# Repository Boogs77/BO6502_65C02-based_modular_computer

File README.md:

# BO6502: 65C02-Based Modular Computer System

Technical overview of the **BO6502** core architecture. This system leverages the iconic 6502 instruction set with modern, high-reliability components from Western Design Center, Atmel, and Hitachi, offering a versatile platform for retro-computing enthusiasts.

---

## 🧠 Processing Core & System Control

The system is built around a modular 39-pin bus (36 signals + 3 spares) distributed via a robust backplane.

| Module | Type | Status | Description |
| :--- | :--- | :--- | :--- |
| **[CPU Module](https://github.com/Boogs77/BO6502/tree/main/BO6502%20CPU)** |  |  | Central Processing Unit W65C02S. |
| **[Reset & Clock](https://github.com/Boogs77/BO6502/tree/main/BO6502%20RESET)** |  |  | NE555 Reset and switchable clock (2MHz/1MHz/500kHz). |
| **[Backplate](https://github.com/Boogs77/BO6502/tree/main/BO6502%20BACKPLATE)** |  |  | The 39-pin bus backbone with voltage regulation. |
| **[Bridge Connector](https://github.com/Boogs77/BO6502/tree/main/BO6502%20CONNECTOR)** |  |  | Interconnect for daisy-chaining multiple backplates. |

---

## 💾 Memory Map & Storage

The system features a balanced 64KB memory architecture, divided between high-speed static RAM and non-volatile storage.

### [RAM Module](https://github.com/Boogs77/BO6502/tree/main/BO6502%20RAM) ($0000 - $7FFF)
* **Chip**: HITACHI **HM62256LP-12** (32KB SRAM).
* **Status**: 
* **Features**: Revision 02 includes **8 exclusion jumpers** (J-CS0 to J-CS7) to carve out space for I/O modules. Includes JP4 to bypass system clock triggering.
* **PCB**: [RAM_final_rev02](https://github.com/Boogs77/BO6502/blob/main/BO6502%20RAM/gallery/RAM_final_rev02.png?raw=true).

### [ROM Module](https://github.com/Boogs77/BO6502/tree/main/BO6502%20ROM) ($8000 - $FFFF)
* **Chip**: ATMEL **AT28C256** (32KB EEPROM).
* **Status**: 
* **Features**: Equipped with a **ZIF socket** for easy updates. The "Multi" version uses jumpers (J-CS3, CS4, CS5) to disable ROM in specific ranges for advanced peripherals.
* **PCBs**: [Base](https://github.com/Boogs77/BO6502_65C02-based_modular_computer/blob/main/BO6502%20ROM/gallery/ROM_final_rev01.png?raw=true) | [24K Test](https://github.com/Boogs77/BO6502_65C02-based_modular_computer/blob/main/BO6502%20ROM/gallery/ROM24k_final_rev01.png?raw=true) | [Multi-Selection](https://github.com/Boogs77/BO6502_65C02-based_modular_computer/blob/main/BO6502%20ROM/gallery/ROMmulti_final_rev01.png?raw=true).

---

## 🔌 Peripheral & I/O Addressing

Peripheral addressing is managed via **74LS138** decoders to ensure precise memory mapping and avoid bus contention.

| Module | Type | Status | Address | PCB Link |
| :--- | :--- | :--- | :--- | :--- |
| **[VDU Module](https://github.com/Boogs77/BO6502/tree/main/BO6502%20VDU)** |  |  | **$BXXX** | [VDU PCB](https://github.com/Boogs77/BO6502_65C02-based_modular_computer/blob/main/BO6502%20VDU/gallery/VDU_TMS_final_rev01.png?raw=true) |
| **[Serial I/O](https://github.com/Boogs77/BO6502/tree/main/BO6502%20SERIAL)** |  |  | **$CXXX** | [Serial PCB](https://github.com/Boogs77/BO6502_65C02-based_modular_computer/blob/main/BO6502%20SERIAL/gallery/Serial_final_rev03.png?raw=true) |
| **[SD Card](https://github.com/Boogs77/BO6502/tree/main/BO6502%20SDCard)** |  |  | **$D1BX** | [SD Card PCB](https://github.com/Boogs77/BO6502_65C02-based_modular_computer/blob/main/BO6502%20SDCard/gallery/SDcard_final_rev02%20v2.png?raw=true) |
| **[Standalone Keyb](https://github.com/Boogs77/BO6502/tree/main/BO6502%20KEYb)** |  |  | **$D18X** | [Keyboard PCB](https://github.com/Boogs77/BO6502/blob/main/BO6502%20KEYb/gallery/KEYb_final-rev01.png?raw=true) |
| **[Big LCD Module](https://github.com/Boogs77/BO6502/tree/main/BO6502%20BIGLCD)** |  |  | **$D19X** | [Big LCD Module](https://github.com/Boogs77/BO6502/blob/main/BO6502%20BIGLCD/README.md) |
| **[Legacy LCD/Keyb](https://github.com/Boogs77/BO6502/tree/main/BO6502%20LCD_KEYb)** |  |  | **$DXXX** | [Legacy PCB](https://github.com/Boogs77/BO6502/blob/main/BO6502%20LCD_KEYb/gallery/LCD_KEYb_final_rev02.png?raw=true) |

---

## 📺 Visual Output Tiers

* **Pro**: **TMS9918A** VDU Module with 32KB dedicated RAM. Supports NTSC Composite Out, Sprites, and 16 Colors.
* **Advanced**: **Toshiba T6963** Graphical LCD (160x128 Pixels).
* **Basic**: **Hitachi HD44780U** 16x2 Character LCD.

---

## 🛠 Diagnostic & Testing Tools

| Module | Type | Status | Function | PCB Link |
| :--- | :--- | :--- | :--- | :--- |
| **[Monitor Interface](https://github.com/Boogs77/BO6502/tree/main/BO6502%20MONITOR)** |  |  | Arduino Mega Bus Sniffer (Ben Eater style). | [Monitor PCB](https://github.com/Boogs77/BO6502/blob/main/BO6502%20MONITOR/gallery/MONITOR_final_rev01.png?raw=true) |
| **[LED Test Board](https://github.com/Boogs77/BO6502/tree/main/BO6502%20LED)** |  |  | Visual 16-LED debug for VIA 65C22 ports. | [LED PCB](https://github.com/Boogs77/BO6502/blob/main/BO6502%20LED/gallery/led_final.png?raw=true) |

---

## 📐 Important Technical Notes

### Jumper Configuration for Advanced Modules
When using the latest system modules (VDU, Joystick, SD Card, etc.), the **ROM** and **RAM** modules must be configured to prevent address conflicts:
- **ROM J-CS3/CS4/CS5**: Set to **VCC** to disable ROM in those specific I/O ranges.
- **SD Card Access**: Provides **Raw Data Access** via bit-banged SPI (PA1=MISO, PA2=MOSI, PA3=SCK, PA4=CS).

---
© 2026 Boogs77 | BO6502 Project - Technical Documentation.

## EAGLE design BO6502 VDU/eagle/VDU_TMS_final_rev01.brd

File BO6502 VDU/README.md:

# BO6502 VDU (Video Display Unit)

The **VDU Module** brings advanced color graphics and video capabilities to the BO6502 system. It is built around the legendary **TMS9918A** Video Display Processor (VDP), the same chip found in iconic systems like the MSX, ColecoVision, and TI-99/4A.

---

## 🛠 Hardware Specifications

The design of this module is the result of extensive research and optimization, integrating modern memory solutions with vintage video hardware.

* **Video Processor:** **TMS9918A** alowing for multiple video modes, including 15 colors plus transparent, and sprite support.
* **Video RAM:** Utilizes an **HM62256** (32KB SRAM) chip. Although the TMS9918A natively addresses 16KB, this modern SRAM provides a stable and reliable memory interface.
* **Logic Optimization:** Following the analysis of the **[HBC-56 project](https://github.com/visrealm/hbc-56/tree/main/schematics/tms9918)**, the design opts for a **74HCT245** transceiver instead of a third 74HCT574 latch. This choice streamlines the data bus communication between the CPU and the VDP.

### Design References
The architecture is heavily inspired by:
* **Leonardo Milani's work:** [Interfacing a TMS9918A to a 6502](https://www.leonardomiliani.com/?p=1631&lang=en).
* **J.B. Langston's design:** [TMS9918A Interface](https://github.com/jblang/TMS9918A).

---

## 🕹️ Address Decoding ($BXXX)

The module is integrated into the system memory map using a **74HCT138** decoder.

* **Address Range:** The VDU is mapped to the **$BXXX** block.
* **Interface:** The CPU communicates with the VDP via two specific addresses within this range to handle data transfers and register configurations.

---

## 📐 Development & Testing

Before the final PCB production, the board underwent rigorous testing:
* **Arduino Integration:** Extensive tests were performed using an **Arduino Mega** to verify the correct addressing logic and to validate all supported video modes (Text, Multicolour, Graphics I & II).
* **Signal Integrity:** Careful layout was implemented to ensure the composite video output remains clean and free from interference.

---

## 📂 Related Modules
* 🏗️ **[Backplate System](https://github.com/Boogs77/BO6502/blob/main/BO6502%20BACKPLATE/README.md)**: Main 39-pin system bus connection.
* 🧠 **[CPU Module](https://github.com/Boogs77/BO6502/blob/main/BO6502%20CPU/README.md)**: W65C02 central processor.
* 🖥️ **[Monitor Interface](https://github.com/Boogs77/BO6502/blob/main/BO6502%20MONITOR/README.md)**: Used during early VDP register debugging.

---
© 2026 Boogs77 | BO6502 Project - Technical Documentation.

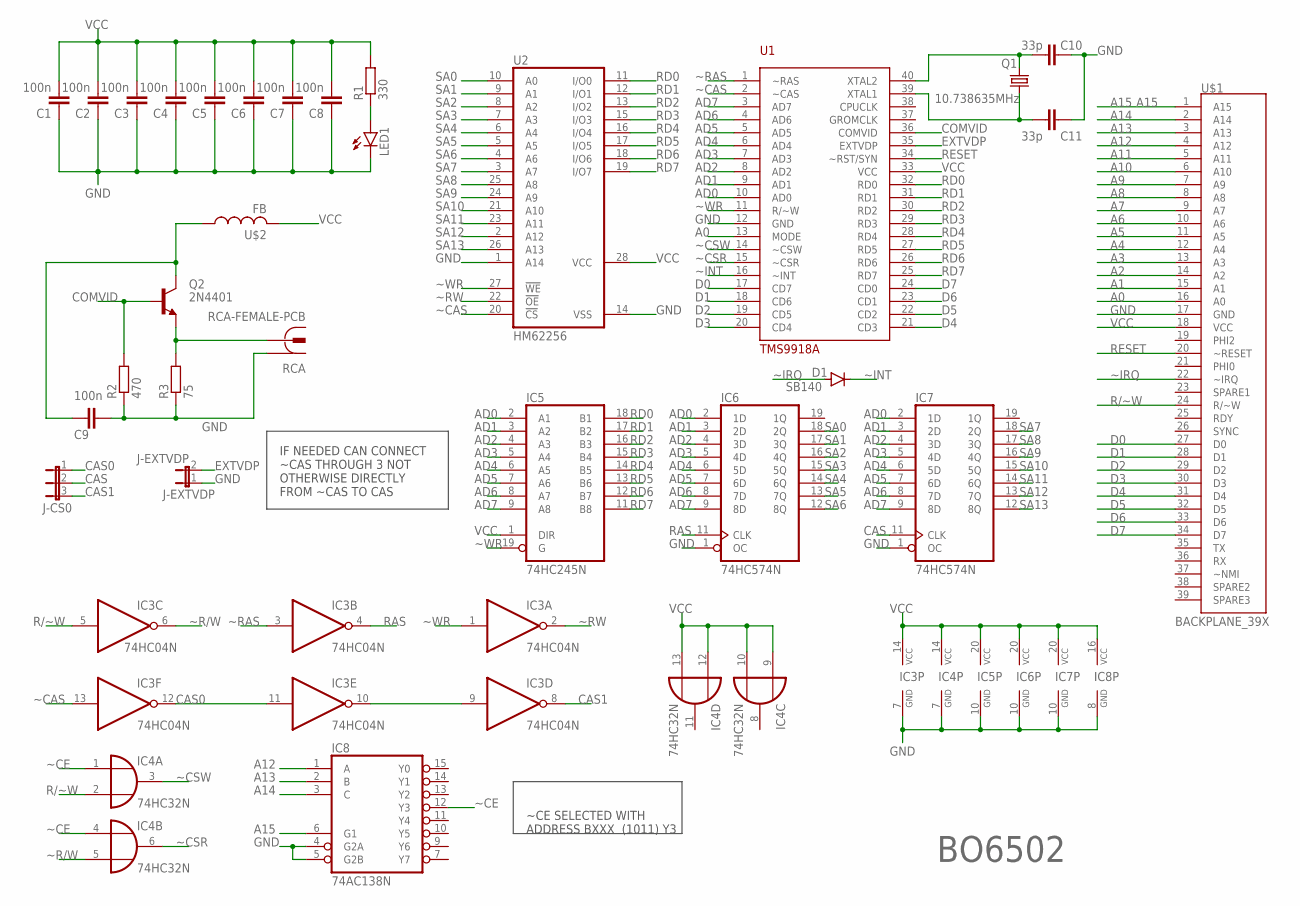
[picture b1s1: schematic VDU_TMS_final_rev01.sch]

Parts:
C1, C2, C3, C4, C5, C6, C7, C8, C9: 100n; C025-025X050
C10, C11: 33p; C025-025X050
D1: SB140; DO41-10
IC3: 74HC04N; DIL14
IC4: 74HC32N; DIL14
IC5: 74HC245N; DIL20
IC6, IC7: 74HC574N; DIL20
IC8: 74AC138N; DIL16
J-CAS: J-CS0; JP2
J-EXTVDP: J-EXTVDP; JP1
LED1: RED; LED5MM
Q1: 10.738635MHz; HC49/S
Q2: 2N4401; TO92-EBC
R1: 330; 0207/10
R2: 470; 0207/10
R3: 75; 0207/10
RCA: RCA-FEMALE-PCB
U1: TMS9918A; DIL40
U2: HM62256; DIL28-6
U$1: BACKPLANE_39X; BP_39X
U$2: FB

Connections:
A0: U1.13 (MODE), U$1.16 (A0)
A1: U$1.15 (A1)
A2: U$1.14 (A2)
A3: U$1.13 (A3)
A4: U$1.12 (A4)
A5: U$1.11 (A5)
A6: U$1.10 (A6)
A7: U$1.9 (A7)
A8: U$1.8 (A8)
A9: U$1.7 (A9)
A10: U$1.6 (A10)
A11: U$1.5 (A11)
A12: IC8.1 (A), U$1.4 (A12)
A13: IC8.2 (B), U$1.3 (A13)
A14: IC8.3 (C), U$1.2 (A14)
A15: IC8.6 (G1), U$1.1 (A15)
AD0: IC5.2 (A1), IC6.2 (1D), IC7.2 (1D), U1.10 (AD0)
AD1: IC5.3 (A2), IC6.3 (2D), IC7.3 (2D), U1.9 (AD1)
AD2: IC5.4 (A3), IC6.4 (3D), IC7.4 (3D), U1.8 (AD2)
AD3: IC5.5 (A4), IC6.5 (4D), IC7.5 (4D), U1.7 (AD3)
AD4: IC5.6 (A5), IC6.6 (5D), IC7.6 (5D), U1.6 (AD4)
AD5: IC5.7 (A6), IC6.7 (6D), IC7.7 (6D), U1.5 (AD5)
AD6: IC5.8 (A7), IC6.8 (7D), IC7.8 (7D), U1.4 (AD6)
AD7: IC5.9 (A8), IC6.9 (8D), IC7.9 (8D), U1.3 (AD7)
CAS: IC7.11 (CLK), J-CAS.2
CAS0: IC3.11 (I), IC3.12 (O), J-CAS.1
CAS1: IC3.8 (O), J-CAS.3
COMVID: Q2.B, R2.2, U1.36 (COMVID)
D0: U1.17 (CD7), U$1.27 (D0)
D1: U1.18 (CD6), U$1.28 (D1)
D2: U1.19 (CD5), U$1.29 (D2)
D3: U1.20 (CD4), U$1.30 (D3)
D4: U1.21 (CD3), U$1.31 (D4)
D5: U1.22 (CD2), U$1.32 (D5)
D6: U1.23 (CD1), U$1.33 (D6)
D7: U1.24 (CD0), U$1.34 (D7)
EXTVDP: J-EXTVDP.2, U1.35 (EXTVDP)
GND: C1.1, C2.1, C3.1, C4.1, C5.1, C6.1, C7.1, C8.1, C9.1, C10.1, C11.1, IC3.7 (GND), IC4.7 (GND), IC5.10 (GND), IC6.1 (OC), IC6.10 (GND), IC7.1 (OC), IC7.10 (GND), IC8.4 (G2A), IC8.5 (G2B), IC8.8 (GND), J-EXTVDP.1, LED1.K (C), R2.1, R3.1, RCA.1, U1.12 (GND), U2.1 (A14), U2.14 (VSS), U$1.17 (GND)
unnamed: Q2.E, R3.2, RCA.2@1 (2), RCA.2@2 (2)
unnamed: C9.2, Q2.C, U$2.P$1 (1)
unnamed: C10.2, Q1.2, U1.40 (XTAL2)
unnamed: LED1.A, R1.1
unnamed: C11.2, Q1.1, U1.39 (XTAL1)
unnamed: IC3.9 (I), IC3.10 (O)
R/~W: IC3.5 (I), IC4.2 (I1), U$1.24 (R/~W)
RAS: IC3.4 (O), IC6.11 (CLK)
RD0: IC5.18 (B1), U1.32 (RD0), U2.11 (I/O0)
RD1: IC5.17 (B2), U1.31 (RD1), U2.12 (I/O1)
RD2: IC5.16 (B3), U1.30 (RD2), U2.13 (I/O2)
RD3: IC5.15 (B4), U1.29 (RD3), U2.15 (I/O3)
RD4: IC5.14 (B5), U1.28 (RD4), U2.16 (I/O4)
RD5: IC5.13 (B6), U1.27 (RD5), U2.17 (I/O5)
RD6: IC5.12 (B7), U1.26 (RD6), U2.18 (I/O6)
RD7: IC5.11 (B8), U1.25 (RD7), U2.19 (I/O7)
RESET: U1.34 (~RST/SYN), U$1.20 (~RESET)
SA0: IC6.18 (2Q), U2.10 (A0)
SA1: IC6.17 (3Q), U2.9 (A1)
SA2: IC6.16 (4Q), U2.8 (A2)
SA3: IC6.15 (5Q), U2.7 (A3)
SA4: IC6.14 (6Q), U2.6 (A4)
SA5: IC6.13 (7Q), U2.5 (A5)
SA6: IC6.12 (8Q), U2.4 (A6)
SA7: IC7.18 (2Q), U2.3 (A7)
SA8: IC7.17 (3Q), U2.25 (A8)
SA9: IC7.16 (4Q), U2.24 (A9)
SA10: IC7.15 (5Q), U2.21 (A10)
SA11: IC7.14 (6Q), U2.23 (A11)
SA12: IC7.13 (7Q), U2.2 (A12)
SA13: IC7.12 (8Q), U2.26 (A13)
VCC: C1.2, C2.2, C3.2, C4.2, C5.2, C6.2, C7.2, C8.2, IC3.14 (VCC), IC4.9 (I0), IC4.10 (I1), IC4.12 (I0), IC4.13 (I1), IC4.14 (VCC), IC5.1 (DIR), IC5.20 (VCC), IC6.20 (VCC), IC7.20 (VCC), IC8.16 (VCC), R1.2, U1.33 (VCC), U2.28 (VCC), U$1.18 (VCC), U$2.P$2 (2)
~CAS: IC3.13 (I), U1.2 (~CAS), U2.20 (!CS)
~CE: IC4.1 (I0), IC4.4 (I0), IC8.12 (Y3)
~CSR: IC4.6 (O), U1.15 (~CSR)
~CSW: IC4.3 (O), U1.14 (~CSW)
~INT: D1.C, U1.16 (~INT)
~IRQ: D1.A, U$1.22 (~IRQ)
~R/W: IC3.6 (O), IC4.5 (I1)
~RAS: IC3.3 (I), U1.1 (~RAS)
~RW: IC3.2 (O), U2.22 (!OE)
~WR: IC3.1 (I), IC5.19 (G), U1.11 (R/~W), U2.27 (!WE)

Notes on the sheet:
BO6502
IF NEEDED CAN CONNECT ~CAS THROUGH 3 NOT OTHERWISE DIRECTLY FROM ~CAS TO CAS
~CE SELECTED WITH ADDRESS BXXX (1011) Y3

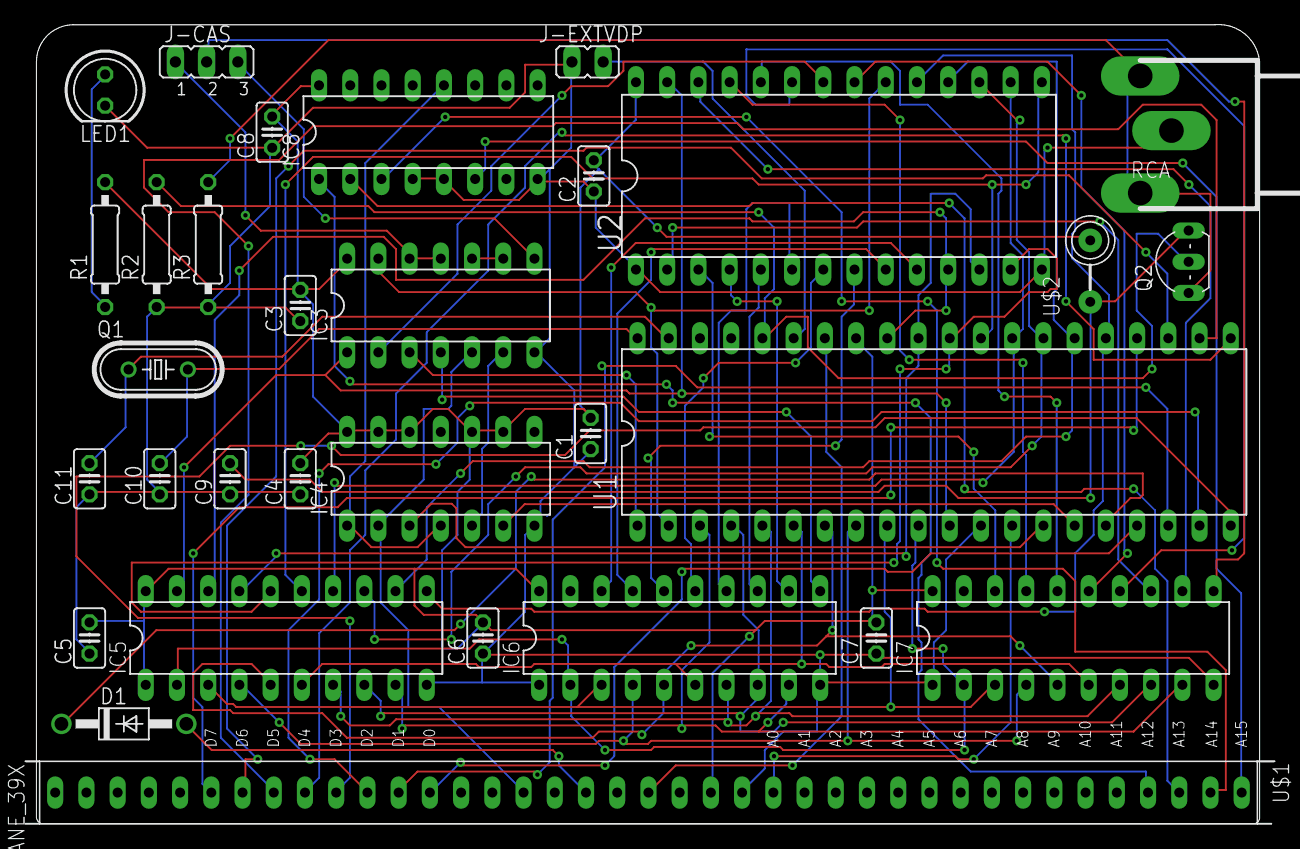
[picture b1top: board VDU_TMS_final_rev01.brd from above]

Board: 2 copper layers, 101.6 x 65.0 mm, 31 parts (0 on the bottom side), 69 nets.

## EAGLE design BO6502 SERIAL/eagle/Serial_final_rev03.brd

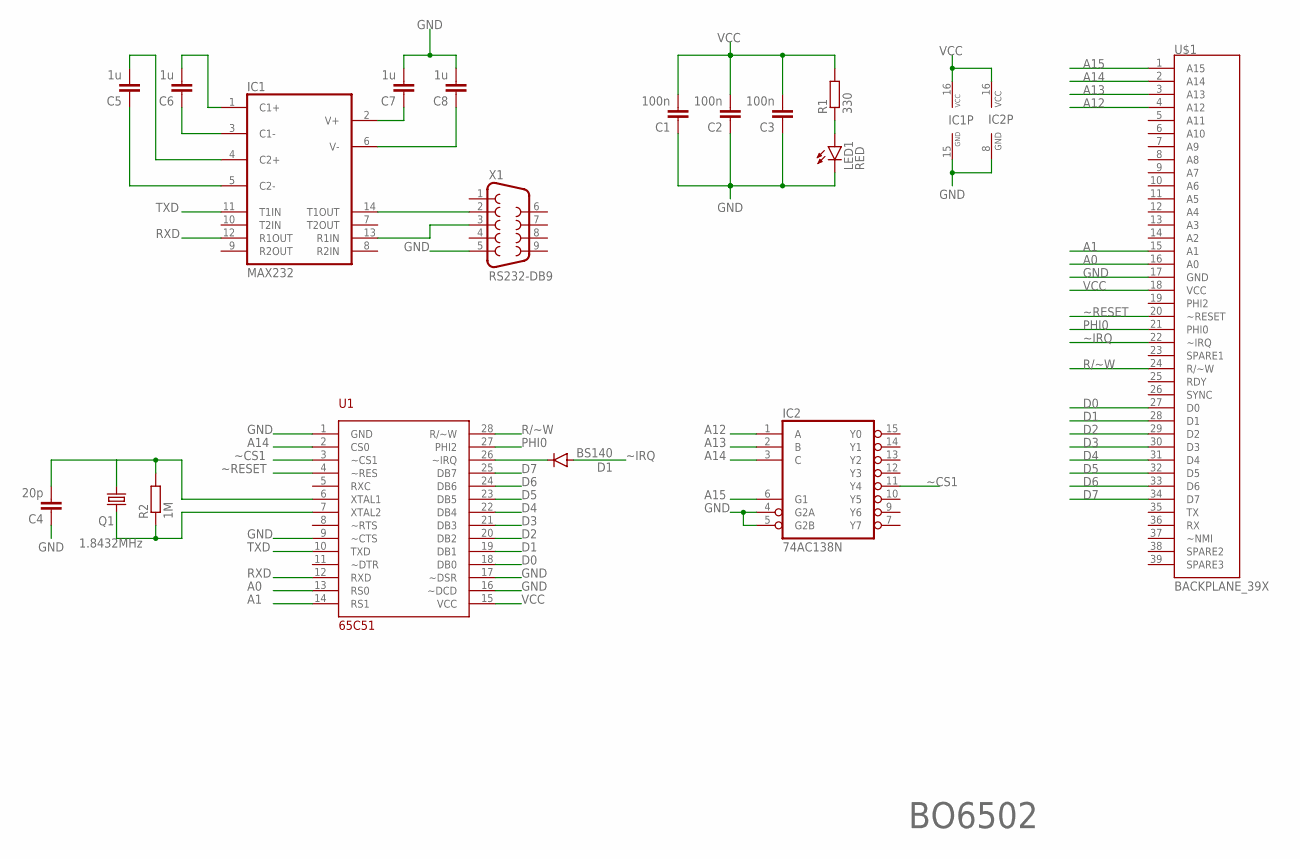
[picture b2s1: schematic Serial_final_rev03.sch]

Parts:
C1, C2, C3: 100n; C025-025X050
C4: 20p; C025-025X050
C5, C6, C7, C8: 1u; C050-025X075
D1: BS140; DO41-10
IC1: MAX232; DIL16
IC2: 74AC138N; DIL16
LED1: RED; LED5MM
Q1: 1.8432MHz; HC49/S
R1: 330; 0207/10
R2: 1M; 0207/10
U1: 65C51; DIL28
U$1: BACKPLANE_39X; BP_39X
X1: RS232-DB9; F09HP

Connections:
A0: U1.13 (RS0), U$1.16 (A0)
A1: U1.14 (RS1), U$1.15 (A1)
A12: IC2.1 (A), U$1.4 (A12)
A13: IC2.2 (B), U$1.3 (A13)
A14: IC2.3 (C), U1.2 (CS0), U$1.2 (A14)
A15: IC2.6 (G1), U$1.1 (A15)
D0: U1.18 (DB0), U$1.27 (D0)
D1: U1.19 (DB1), U$1.28 (D1)
D2: U1.20 (DB2), U$1.29 (D2)
D3: U1.21 (DB3), U$1.30 (D3)
D4: U1.22 (DB4), U$1.31 (D4)
D5: U1.23 (DB5), U$1.32 (D5)
D6: U1.24 (DB6), U$1.33 (D6)
D7: U1.25 (DB7), U$1.34 (D7)
GND: C1.1, C2.1, C3.1, C4.1, C7.2, C8.2, IC1.15 (GND), IC2.4 (G2A), IC2.5 (G2B), IC2.8 (GND), LED1.K (C), U1.1 (GND), U1.9 (~CTS), U1.16 (~DCD), U1.17 (~DSR), U$1.17 (GND), X1.5
unnamed: C6.2, IC1.1 (C1+)
unnamed: D1.C, U1.26 (~IRQ)
unnamed: C6.1, IC1.3 (C1-)
unnamed: C5.2, IC1.4 (C2+)
unnamed: C5.1, IC1.5 (C2-)
unnamed: LED1.A, R1.1
unnamed: IC1.14 (T1OUT), X1.2
unnamed: IC1.13 (R1IN), X1.3
unnamed: C7.1, IC1.2 (V+)
unnamed: C8.1, IC1.6 (V-)
unnamed: C4.2, Q1.2, R2.2, U1.6 (XTAL1)
unnamed: Q1.1, R2.1, U1.7 (XTAL2)
PHI0: U1.27 (PHI2), U$1.21 (PHI0)
R/~W: U1.28 (R/~W), U$1.24 (R/~W)
RXD: IC1.12 (R1OUT), U1.12 (RXD)
TXD: IC1.11 (T1IN), U1.10 (TXD)
VCC: C1.2, C2.2, C3.2, IC1.16 (VCC), IC2.16 (VCC), R1.2, U1.15 (VCC), U$1.18 (VCC)
~CS1: IC2.11 (Y4), U1.3 (~CS1)
~IRQ: D1.A, U$1.22 (~IRQ)
~RESET: U1.4 (~RES), U$1.20 (~RESET)

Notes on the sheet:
BO6502

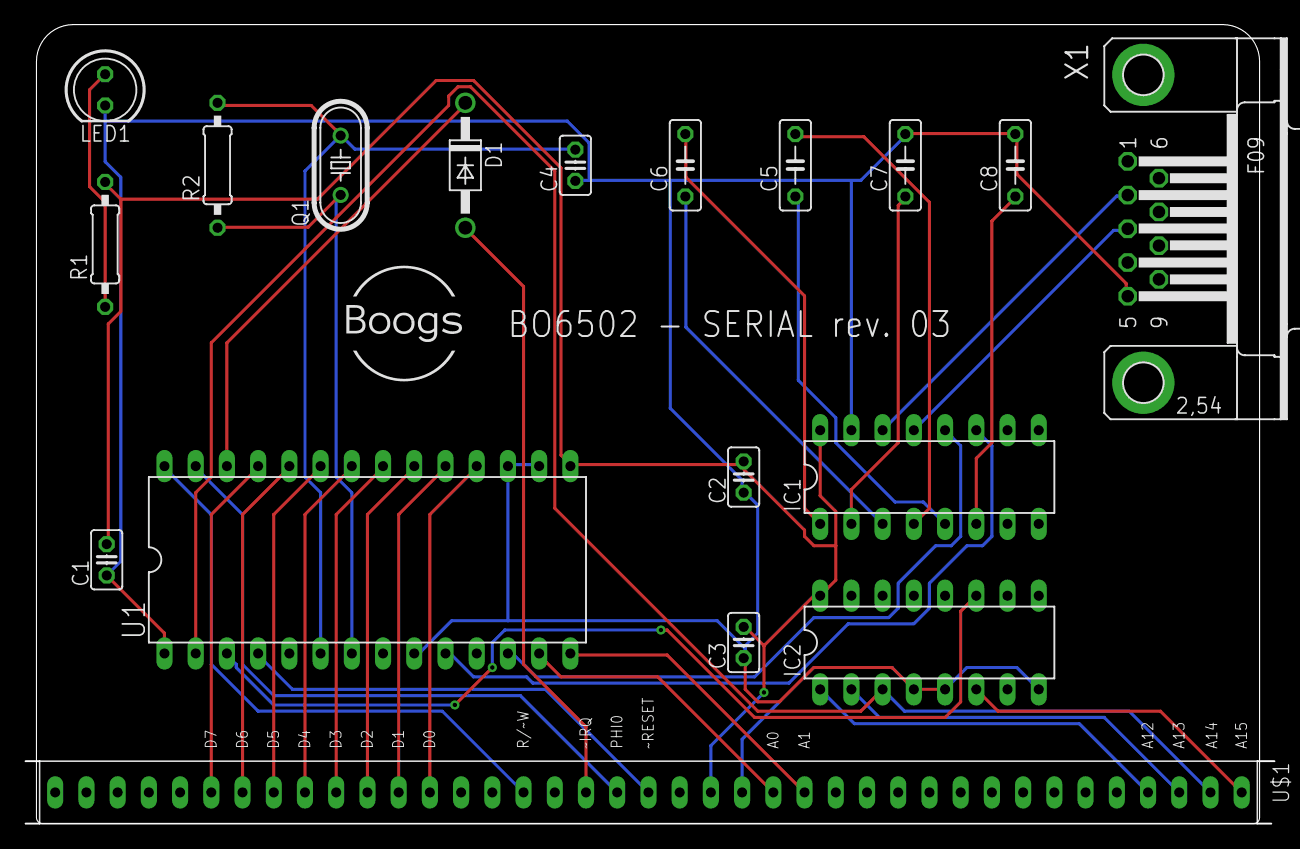
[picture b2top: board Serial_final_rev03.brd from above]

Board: 2 copper layers, 101.6 x 65.0 mm, 18 parts (0 on the bottom side), 35 nets.

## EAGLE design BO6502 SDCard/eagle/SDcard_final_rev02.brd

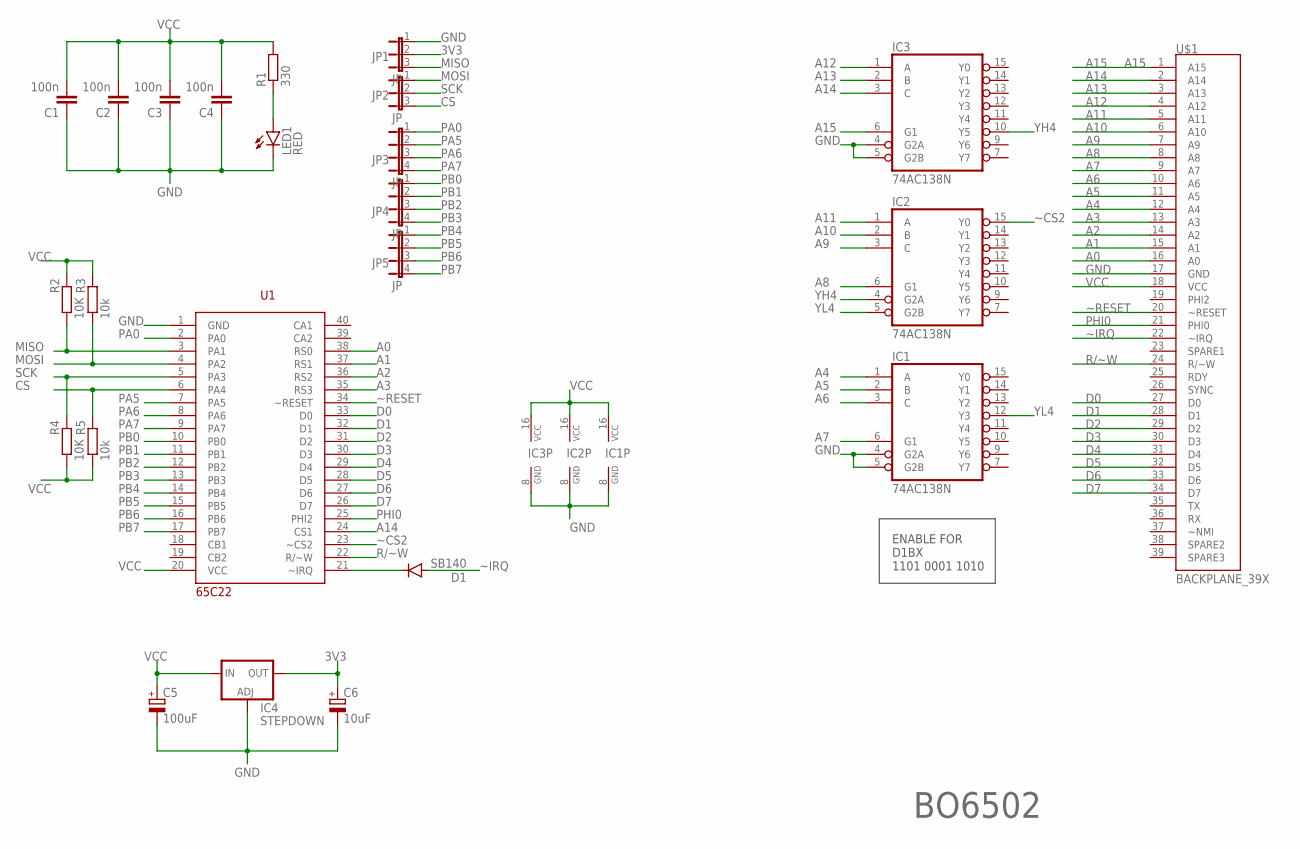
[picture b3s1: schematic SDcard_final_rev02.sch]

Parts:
C1, C2, C3, C4: 100n; C025-025X050
C5: 100uF; B45181A
C6: 10uF; B45181A
D1: SB140; DO41-10
IC1, IC2, IC3: 74AC138N; DIL16
IC4: STEPDOWN; 317TS
JP1, JP2: JP; JP2
JP3, JP4, JP5: JP; JP4
LED1: RED; LED5MM
R1: 330; 0207/10
R2, R4: 10K; 0207/10
R3, R5: 10k; 0207/10
U1: 65C22; DIL40
U$1: BACKPLANE_39X; BP_39X

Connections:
3V3: C6.+, IC4.2 (OUT), JP1.2
A0: U1.38 (RS0), U$1.16 (A0)
A1: U1.37 (RS1), U$1.15 (A1)
A2: U1.36 (RS2), U$1.14 (A2)
A3: U1.35 (RS3), U$1.13 (A3)
A4: IC1.1 (A), U$1.12 (A4)
A5: IC1.2 (B), U$1.11 (A5)
A6: IC1.3 (C), U$1.10 (A6)
A7: IC1.6 (G1), U$1.9 (A7)
A8: IC2.6 (G1), U$1.8 (A8)
A9: IC2.3 (C), U$1.7 (A9)
A10: IC2.2 (B), U$1.6 (A10)
A11: IC2.1 (A), U$1.5 (A11)
A12: IC3.1 (A), U$1.4 (A12)
A13: IC3.2 (B), U$1.3 (A13)
A14: IC3.3 (C), U1.24 (CS1), U$1.2 (A14)
A15: IC3.6 (G1), U$1.1 (A15)
CS: JP2.3, R5.2, U1.6 (PA4)
D0: U1.33 (D0), U$1.27 (D0)
D1: U1.32 (D1), U$1.28 (D1)
D2: U1.31 (D2), U$1.29 (D2)
D3: U1.30 (D3), U$1.30 (D3)
D4: U1.29 (D4), U$1.31 (D4)
D5: U1.28 (D5), U$1.32 (D5)
D6: U1.27 (D6), U$1.33 (D6)
D7: U1.26 (D7), U$1.34 (D7)
GND: C1.1, C2.1, C3.1, C4.1, C5.-, C6.-, IC1.4 (G2A), IC1.5 (G2B), IC1.8 (GND), IC2.8 (GND), IC3.4 (G2A), IC3.5 (G2B), IC3.8 (GND), IC4.1 (ADJ), JP1.1, LED1.K (C), U1.1 (GND), U$1.17 (GND)
MISO: JP1.3, R2.1, U1.3 (PA1)
MOSI: JP2.1, R3.1, U1.4 (PA2)
unnamed: D1.C, U1.21 (~IRQ)
unnamed: LED1.A, R1.1
PA0: JP3.1, U1.2 (PA0)
PA5: JP3.2, U1.7 (PA5)
PA6: JP3.3, U1.8 (PA6)
PA7: JP3.4, U1.9 (PA7)
PB0: JP4.1, U1.10 (PB0)
PB1: JP4.2, U1.11 (PB1)
PB2: JP4.3, U1.12 (PB2)
PB3: JP4.4, U1.13 (PB3)
PB4: JP5.1, U1.14 (PB4)
PB5: JP5.2, U1.15 (PB5)
PB6: JP5.3, U1.16 (PB6)
PB7: JP5.4, U1.17 (PB7)
PHI0: U1.25 (PHI2), U$1.21 (PHI0)
R/~W: U1.22 (R/~W), U$1.24 (R/~W)
SCK: JP2.2, R4.2, U1.5 (PA3)
VCC: C1.2, C2.2, C3.2, C4.2, C5.+, IC1.16 (VCC), IC2.16 (VCC), IC3.16 (VCC), IC4.3 (IN), R1.2, R2.2, R3.2, R4.1, R5.1, U1.20 (VCC), U$1.18 (VCC)
YH4: IC2.4 (G2A), IC3.10 (Y5)
YL4: IC1.12 (Y3), IC2.5 (G2B)
~CS2: IC2.15 (Y0), U1.23 (~CS2)
~IRQ: D1.A, U$1.22 (~IRQ)
~RESET: U1.34 (~RESET), U$1.20 (~RESET)

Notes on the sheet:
BO6502
ENABLE FOR D1BX 1101 0001 1010

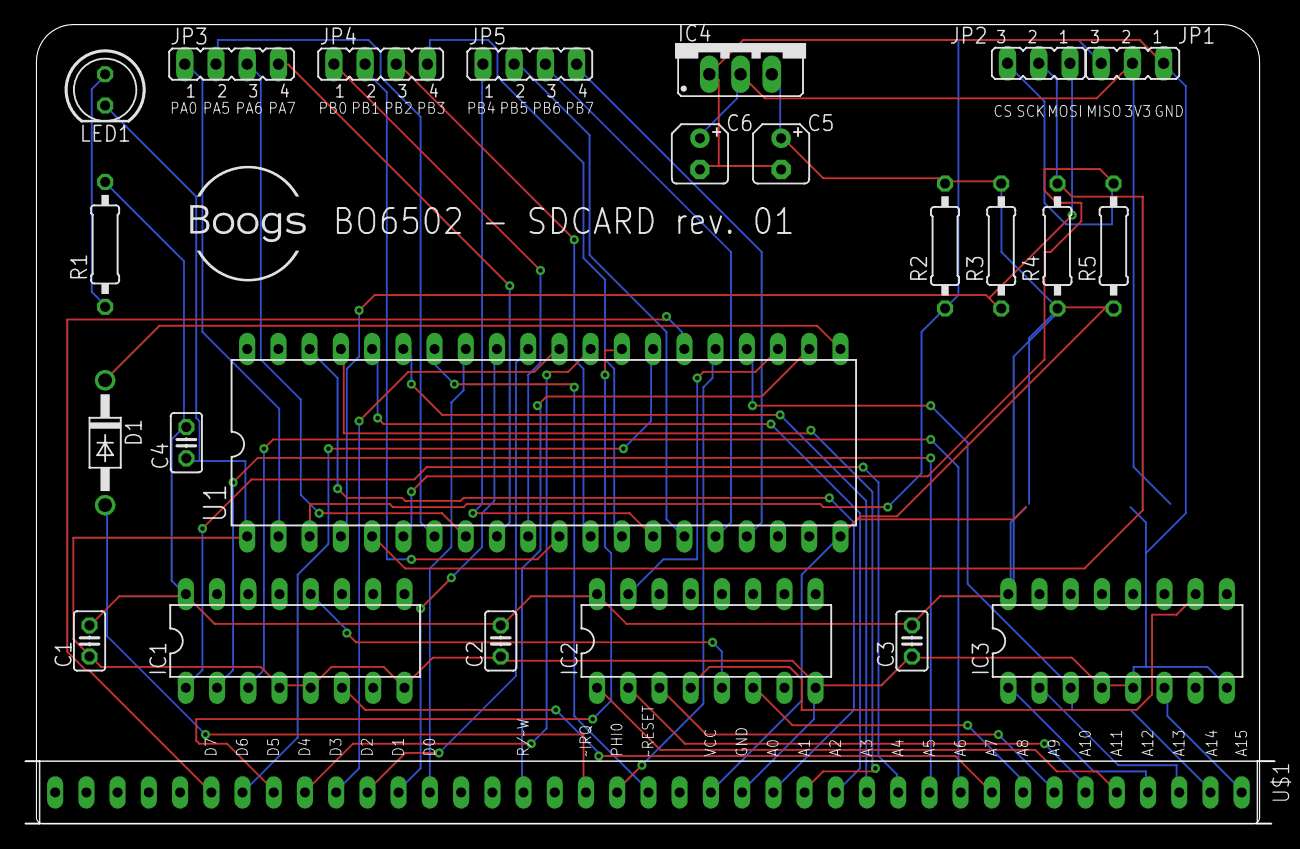
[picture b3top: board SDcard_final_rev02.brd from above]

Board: 2 copper layers, 101.6 x 65.0 mm, 24 parts (0 on the bottom side), 52 nets.

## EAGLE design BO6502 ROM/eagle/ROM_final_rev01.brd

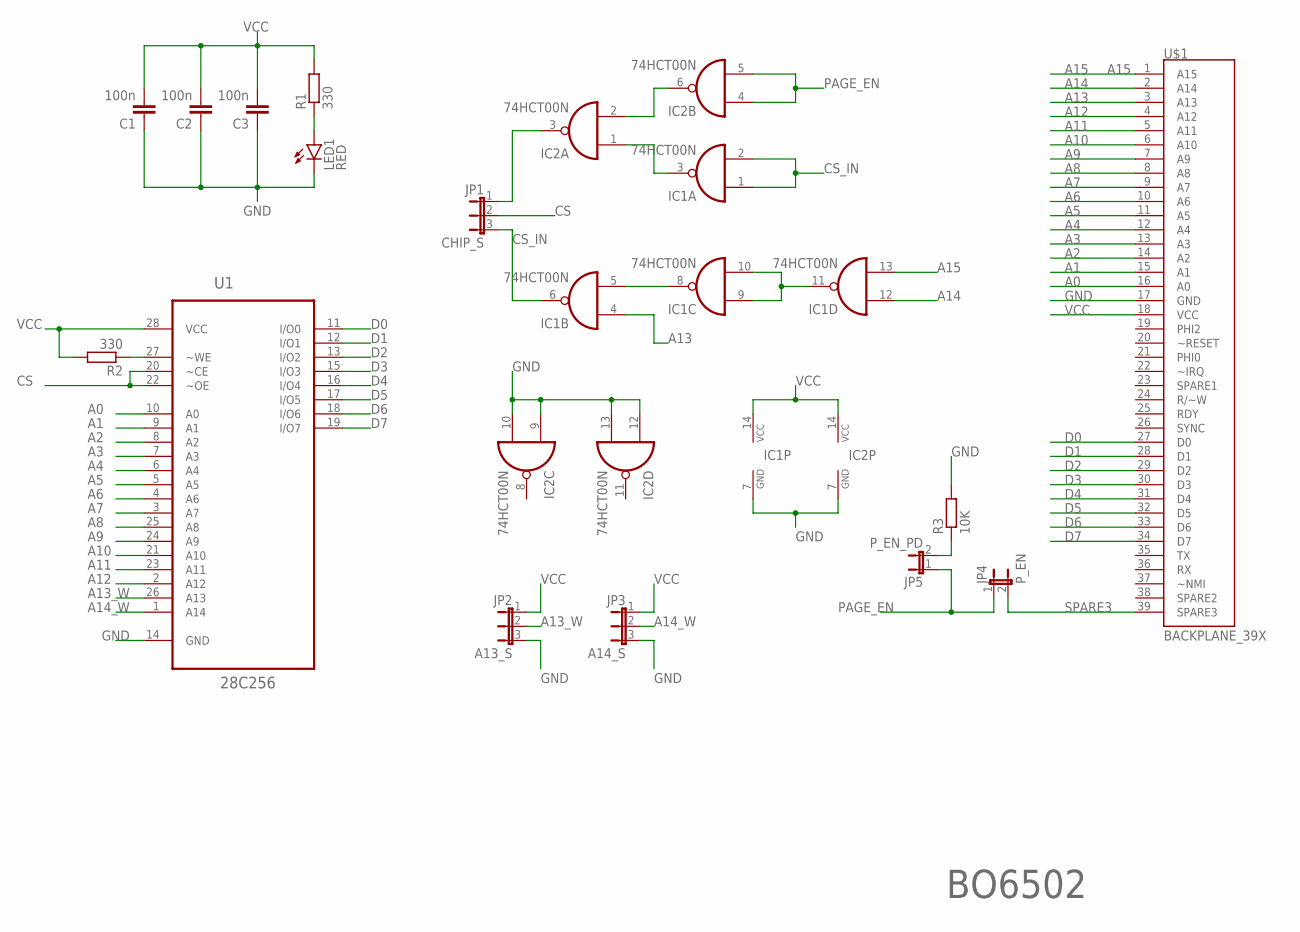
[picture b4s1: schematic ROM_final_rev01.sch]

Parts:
C1, C2, C3: 100n; C025-025X050
IC1, IC2: 74HCT00N; DIL14
JP1: CHIP_S; JP2
JP2: A13_S; JP2
JP3: A14_S; JP2
JP4: P_EN; JP1
JP5: P_EN_PD; JP1
LED1: RED; LED5MM
R1, R2: 330; 0207/10
R3: 10K; 0207/10
U1: 28C256; DIP254P1524X482-28
U$1: BACKPLANE_39X; BP_39X

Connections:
A0: U1.10 (A0), U$1.16 (A0)
A1: U1.9 (A1), U$1.15 (A1)
A2: U1.8 (A2), U$1.14 (A2)
A3: U1.7 (A3), U$1.13 (A3)
A4: U1.6 (A4), U$1.12 (A4)
A5: U1.5 (A5), U$1.11 (A5)
A6: U1.4 (A6), U$1.10 (A6)
A7: U1.3 (A7), U$1.9 (A7)
A8: U1.25 (A8), U$1.8 (A8)
A9: U1.24 (A9), U$1.7 (A9)
A10: U1.21 (A10), U$1.6 (A10)
A11: U1.23 (A11), U$1.5 (A11)
A12: U1.2 (A12), U$1.4 (A12)
A13: IC1.4 (I0), U$1.3 (A13)
A13_W: JP2.2, U1.26 (A13)
A14: IC1.12 (I0), U$1.2 (A14)
A14_W: JP3.2, U1.1 (A14)
A15: IC1.13 (I1), U$1.1 (A15)
CS: JP1.2, U1.20 (~CE), U1.22 (~OE)
CS_IN: IC1.1 (I0), IC1.2 (I1), IC1.6 (O), JP1.3
D0: U1.11 (I/O0), U$1.27 (D0)
D1: U1.12 (I/O1), U$1.28 (D1)
D2: U1.13 (I/O2), U$1.29 (D2)
D3: U1.15 (I/O3), U$1.30 (D3)
D4: U1.16 (I/O4), U$1.31 (D4)
D5: U1.17 (I/O5), U$1.32 (D5)
D6: U1.18 (I/O6), U$1.33 (D6)
D7: U1.19 (I/O7), U$1.34 (D7)
GND: C1.1, C2.1, C3.1, IC1.7 (GND), IC2.7 (GND), IC2.9 (I0), IC2.10 (I1), IC2.12 (I0), IC2.13 (I1), JP2.3, JP3.3, LED1.K (C), R3.2, U1.14 (GND), U$1.17 (GND)
unnamed: R2.1, U1.27 (~WE)
unnamed: IC2.2 (I1), IC2.6 (O)
unnamed: IC1.3 (O), IC2.1 (I0)
unnamed: IC2.3 (O), JP1.1
unnamed: IC1.5 (I1), IC1.8 (O)
unnamed: LED1.A, R1.1
unnamed: IC1.9 (I0), IC1.10 (I1), IC1.11 (O)
unnamed: JP5.2, R3.1
PAGE_EN: IC2.4 (I0), IC2.5 (I1), JP4.1, JP5.1
SPARE3: JP4.2, U$1.39 (SPARE3)
VCC: C1.2, C2.2, C3.2, IC1.14 (VCC), IC2.14 (VCC), JP2.1, JP3.1, R1.2, R2.2, U1.28 (VCC), U$1.18 (VCC)

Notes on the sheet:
BO6502

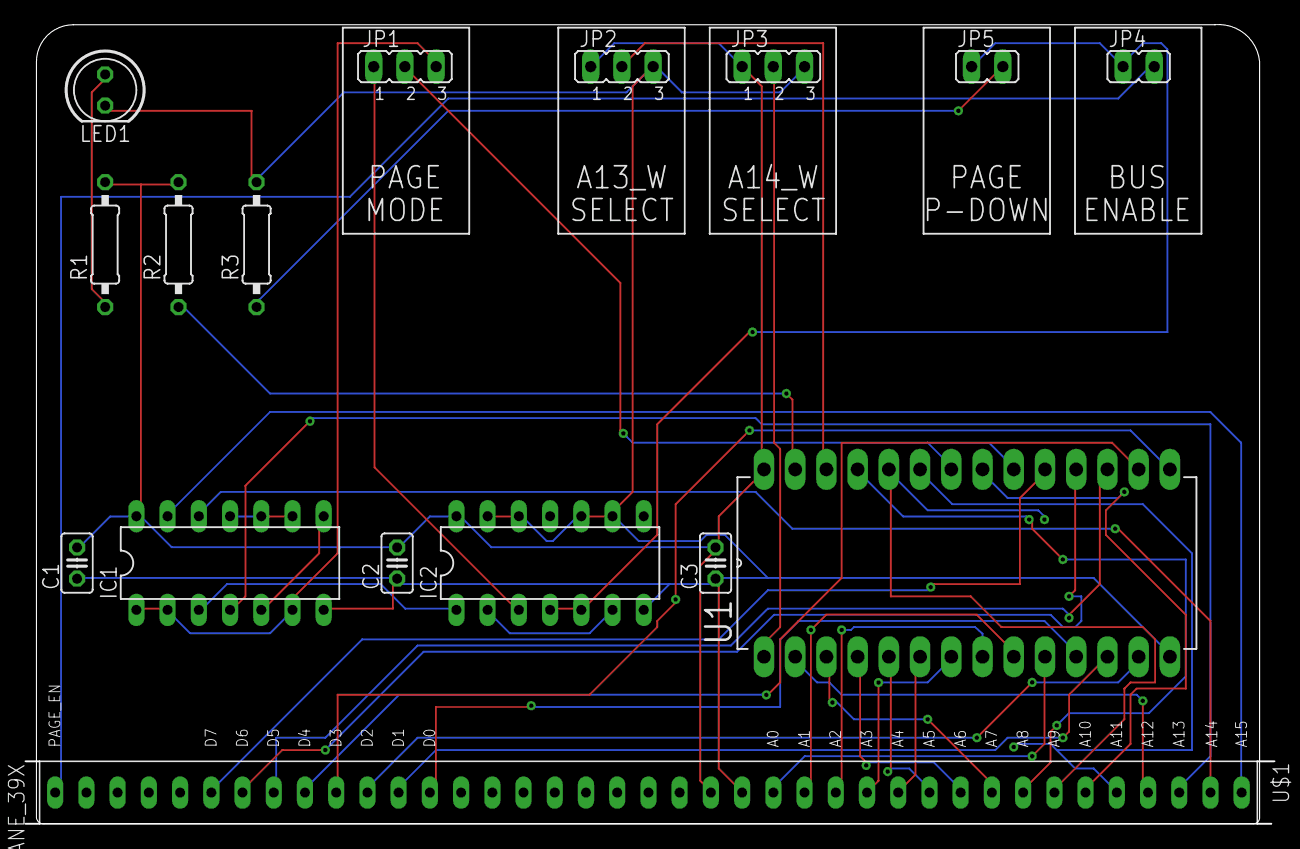
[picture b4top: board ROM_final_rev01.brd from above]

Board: 2 copper layers, 101.6 x 65.0 mm, 16 parts (0 on the bottom side), 40 nets.

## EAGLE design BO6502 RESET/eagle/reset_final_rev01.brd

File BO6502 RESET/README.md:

# BO6502 Reset & Clock Module

The **Reset & Clock Module** is a critical system utility for the BO6502. It provides a reliable power-on reset pulse and a flexible clock generation system to adapt the CPU speed to different hardware requirements.

---

## 🛠 Hardware Specifications

This module combines two essential system functions: power management and timing.

### Reset Circuitry
* **Logic:** Built around the classic **NE555** timer configured in monostable mode.
* **Function:** Ensures a clean and stable active-low RESET pulse upon power-up or manual trigger, ensuring the 65C02 CPU and peripherals initialize correctly.

### Clock Management & Scaling
The board features a flexible clock distribution system, allowing the user to select between different frequencies using a **74LS74** dual flip-flop for frequency division.

* **Direct 2 MHz Clock:** The system can be driven directly by a 2 MHz source (Note: the onboard clock on the CPU module must be disabled when using this configuration).
* **Scaled Frequencies:** Using the 7474 divider, the module can provide:
    * **1 MHz** (Division by 2).
    * **500 kHz** (Further division).
* **Selection:** This allows for high-speed operation or lower speeds for debugging and compatibility with older peripherals.

---

## 🕹️ Integration & Configuration

To use the external clock from this module, ensure the clock jumper/oscillator on the **BO6502 CPU Module** is disconnected to avoid bus contention.

| Frequency | Source / Logic | Recommended Use |
| :--- | :--- | :--- |
| **2 MHz** | Direct Bypass | Standard high-speed operation |
| **1 MHz** | 7474 Divider (Q1) | Standard 6502 compatibility |
| **500 kHz** | 7474 Divider (Q2) | Debugging / Slow peripheral testing |

---

## 📐 Board Layout & Rendering

The layout provides easy access to the reset button and features jumpers for quick frequency switching.

---

## 📂 Related Modules
* 🧠 **[CPU Module](https://github.com/Boogs77/BO6502/blob/main/BO6502%20CPU/README.md)**: W65C02 central processor (requires clock coordination).
* 🏗️ **[Backplate System](https://github.com/Boogs77/BO6502/blob/main/BO6502%20BACKPLATE/README.md)**: Distributes the Reset and Clock signals to all slots.
* 🖥️ **[Monitor Interface](https://github.com/Boogs77/BO6502/blob/main/BO6502%20MONITOR/README.md)**: Used to verify bus activity after a reset.

---
© 2026 Boogs77 | BO6502 Project - Technical Documentation.

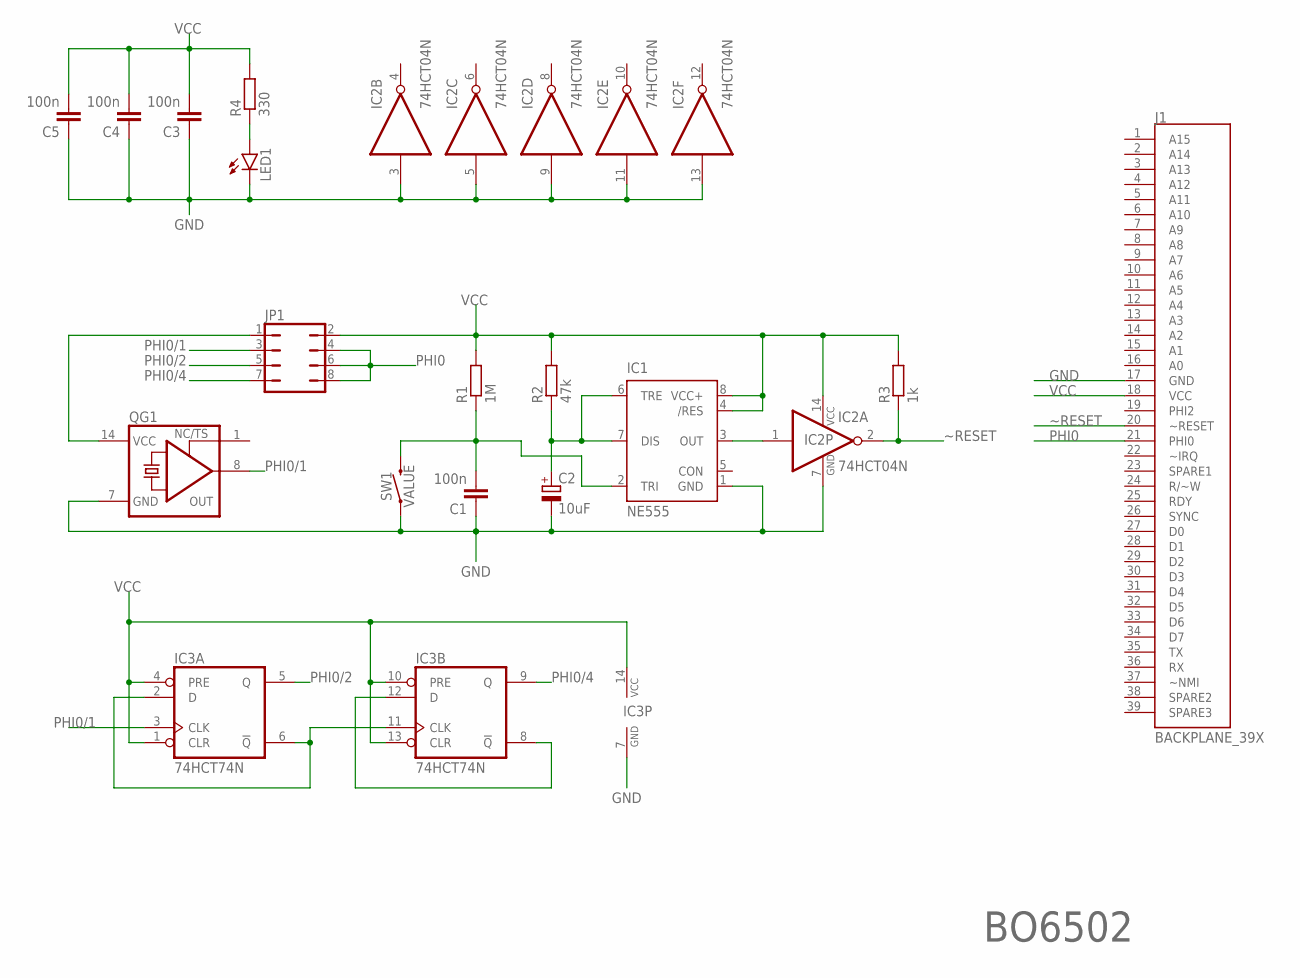
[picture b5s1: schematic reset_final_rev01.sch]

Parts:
C1, C3, C4, C5: 100n; C025-025X050
C2: 10uF; B45181A
IC1: NE555; DIL-08
IC2: 74HCT04N; DIL14
IC3: 74HCT74N; DIL14
J1: BACKPLANE_39X; BP_39X
JP1: JP4Q
LED1: LED5MM
QG1: XO-14; DIL14S
R1: 1M; 0207/10
R2: 47k; 0207/10
R3: 1k; 0207/10
R4: 330; 0207/10
SW1: MOMENTARY-SWITCH-SPST-PTH-6.0MM-KIT; TACTILE_SWITCH_PTH_6.0MM_KIT

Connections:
GND: C1.1, C2.-, C3.1, C4.1, C5.1, IC1.1 (GND), IC2.3 (I), IC2.5 (I), IC2.7 (GND), IC2.9 (I), IC2.11 (I), IC2.13 (I), IC3.7 (GND), J1.17 (GND), LED1.K (C), QG1.7 (GND), SW1.1
unnamed: JP1.1, QG1.14 (VCC)
unnamed: IC1.3 (OUT), IC2.1 (I)
unnamed: C2.+, IC1.6 (TRE), IC1.7 (DIS), R2.1
unnamed: C1.2, IC1.2 (TRI), R1.1, SW1.3 (2)
unnamed: LED1.A, R4.1
unnamed: IC3.2 (D), IC3.6 (!Q), IC3.11 (CLK)
unnamed: IC3.8 (!Q), IC3.12 (D)
PHI0: J1.21 (PHI0), JP1.4, JP1.6, JP1.8
PHI0/1: IC3.3 (CLK), JP1.3, QG1.8 (OUT)
PHI0/2: IC3.5 (Q), JP1.5
PHI0/4: IC3.9 (Q), JP1.7
VCC: C3.2, C4.2, C5.2, IC1.4 (/RES), IC1.8 (VCC+), IC2.14 (VCC), IC3.1 (CLR), IC3.4 (PRE), IC3.10 (PRE), IC3.13 (CLR), IC3.14 (VCC), J1.18 (VCC), JP1.2, R1.2, R2.2, R3.2, R4.2
~RESET: IC2.2 (O), J1.20 (~RESET), R3.1

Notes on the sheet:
BO6502

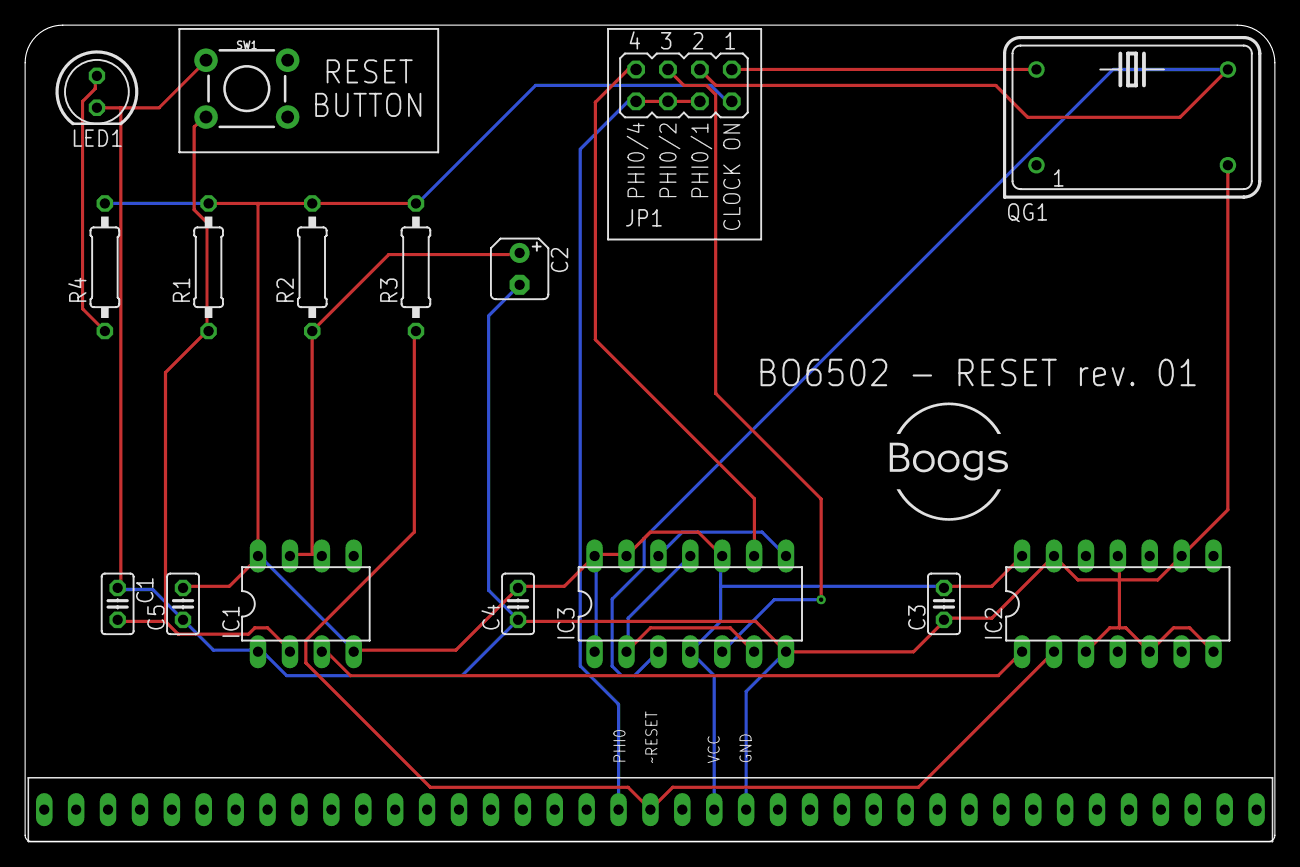
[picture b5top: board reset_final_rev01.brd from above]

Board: 2 copper layers, 99.5 x 65.0 mm, 17 parts (0 on the bottom side), 14 nets.

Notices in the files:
parts and their libraries:
SparkFun-Switches: Licensing: Creative Commons ShareAlike 4.0 International - https://creativecommons.org/licenses/by-sa/4.0
